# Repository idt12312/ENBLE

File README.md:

# ENBLE

ENBLE is the **EN**vironmental sensor which measures temperature, humidity, and air pressure and sends them over **BLE**.
Because it consumes little current, it can work several years.

Using bridge server and [ThingsBooard](https://thingsboard.io/) which are runnning on Raspberry Pi3, 
you can collect data from some ENBLEs and view measurement data via web browser.

## Contents of this repository

This repository consists of two components.

### 1. Sensor 

[**ENBLE/sensor**](sensor/)

It contains PCB design and firmware for a ENBLE device. 
The details is in README.md.

### 2. Bridge Server

[**ENBLE/bridge_server**](bridge_server/)

It constains a bridge between ENBLE and [**ThingsBooard**](https://thingsboard.io/) as a sample code to utilize ENBLE. 
Bridge server listens BLE advertise packets from ENBLEs and sends data to a ThingsBoard server. 
Using ThingsBoard enables you to collect and visualize measured data.

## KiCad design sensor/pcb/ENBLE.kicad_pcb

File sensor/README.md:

# ENBLE Sensor 

This device measures temperature, humidity and pressure using BME280 and send these measured data over BLE advertising and GATT service.
The data format of BLE advertising and GATT service is described bellow.
Using advertising (not using GATT) to collect measured data enables a device to reduce current consumption.  

## BLE Advertise

| Parameter          | Value                 |
|--------------------|-----------------------|
| Local Name         | "ENBLE"               |
| Advertise Interval | 6000ms                |
| Manufacturer data  | 10 bytes binary data  |

ENBLE has a push button.
If you push the button, advertising interval change into 100ms.
It is useful to find the specified device which you press the button. 

Manufacturer data has DeviceID and measurement results of sensors.  
Data format is as shown below. 

| Position | Contents    | DataType |
|----------|-------------|----------|
| byte 0-1 | DeviceID    | uint16   |
| byte 2-3 | Battery     | uint16   |
| byte 4-5 | Temperature | int16    |
| byte 6-7 | Humidity    | uint16   |
| byte 8-9 | Pressure    | uint16   |

Each data is contained in **little endian 16bit integer**.  
Means of above data are same as ones in bellow characteristics.

## BLE Services

| Name          | Type           | Permissions | UUID                                 | DataType |
|---------------|----------------|-------------|--------------------------------------|----------|
| ENBLE Service | Service        | Read        | bff20001-378e-4955-89d6-25948b941062 |          |
| DeviceID      | Characteristic | Read, Write | bff20011-378e-4955-89d6-25948b941062 | uint16   |
|  Period       | Characteristic | Read, Write | bff20012-378e-4955-89d6-25948b941062 | uint16   |
| Battery       | Characteristic | Read        | bff20021-378e-4955-89d6-25948b941062 | uint16   |
| Temperature   | Characteristic | Read        | bff20022-378e-4955-89d6-25948b941062 | int16    |
| Humidity      | Characteristic | Read        | bff20023-378e-4955-89d6-25948b941062 | uint16   |
| Pressure      | Characteristic | Read        | bff20024-378e-4955-89d6-25948b941062 | uint16   |

### DeviceID
This characteristic indicates a unique number as 16bit unsigned integer. 
The value of this characteristic is stored in nonvolatile memory. 

### Period
This characteristic indicates a sample period of sensors. 
All sensors (battery, temperature, humidity and pressure) sample at the same period. 
This period is 16 bit unsigned integer in seconds. 
The value of this characteristic is stored in nonvolatile memory. 

### Battery
This characteristic indicates battery voltage of the device in mV. 

### Temperature
This characteristic indicates temperature in degC, resolution is 0.01 DegC. 
A negative value is represented in two's complement number. 

### Humidity
This characteristic indicates humidity in %, resolution is 0.1 %.

### Pressure
This characteristic indicates air pressure in Pa, resolution is 10Pa

## Build

### Setup for build
1. Download Nordic SDK ver 12.3.0
2. Place Nordic SDK in firmware/lib  
ex) The structure of directory must be is following.   
    firmware/lib/  
        └──nRF5_SDK_12.3.0_d7731ad/ (this directory name can be anything you like)  
        .       ├──components/  
        .       ├──external/  
        .       ├── ......  

3. Modify NORDIC_SDK_PATH parameter in firmware/Makefile
4. Modify toolchain configuration in 
    * for Linux or OSX user : $(NORDIC_SDK_PATH)/components/toolchain/gcc/Makefile.posix
    * for Windows user : $(NORDIC_SDK_PATH)/components/toolchain/gcc/Makefile.windows

### Build and Flash firmware
This project can be build with GNU MAKE. 
What you need to do for build is executing ```make``` command. 
When you flah a firmware to an ENBLE sensor device, 
connect the device via JLink and execute ```make flash```.

## PCB

I design a PCB with KiCad. 

The following is a simple block diagram.

I designed PCB to fit in the case, [**TAKACHI PS-65 Seriese**](http://www.takachi-el.co.jp/data/pdf/2016-01-065.pdf). 

### Current consumption

| State       | Consumption | Interval   |
|-------------|-------------|------------|
| advertising | 29.4 μC     | 6.0 s      |
| measuring (start)   | 4.14 μC     | 60 s       |
| measuring (end)   | 8.07 μC     | 60 s       |
| sleeping    | 3.80 μA     | constantly |

<table border="0">
    <tr>
        <td></td>
        <td></td>
    </tr>
</table>

From the above, current consumption per one hour is  
3600 / 6 * 29.4μ + 3600 / 60 * (4.14μ + 8.07μ) + 3600 * 3.8μ = 32.1 mC/h.

Because CR2032 battery charge is 810C(225mAh), 
ENBLE can work in
810 / 31.6e-3 = 25233h (**about 3 years**).

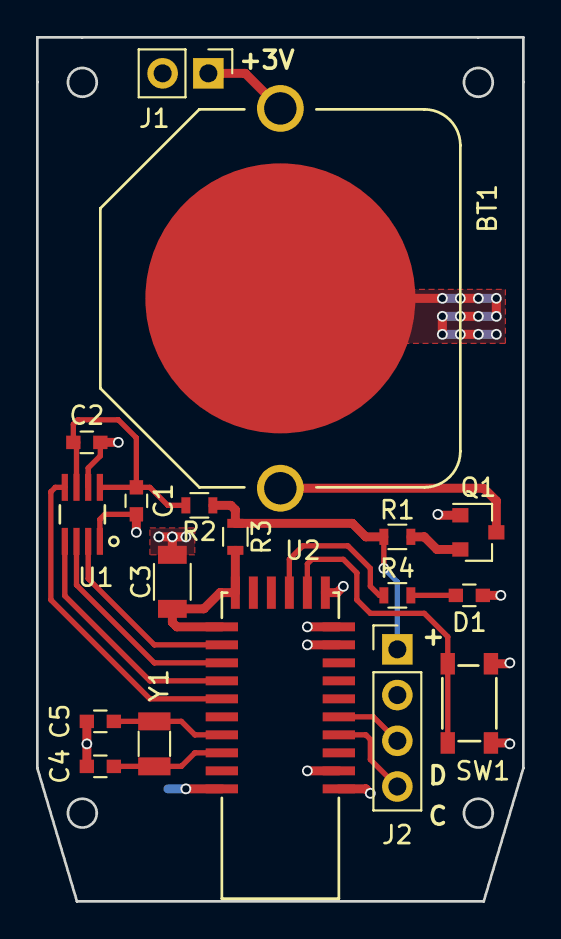
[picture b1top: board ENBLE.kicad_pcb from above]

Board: 2 copper layers, 27.0 x 48.0 mm, 18 parts (0 on the bottom side), 17 nets.

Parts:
BT1: CR2032; BK-888
C1, C2: 0.1u; C_0603
C3: 10u; C_1206
C4, C5: 8p; C_0603
D1: LED; C_0603
J1: Conn_01x02; Pin_Header_Straight_1x02_Pitch2.54mm
J2: Conn_01x04; Pin_Header_Straight_1x04_Pitch2.54mm
Q1: SI2333; SOT-23
R1, R2, R3: 0; R_0603
R4: 2.2k; R_0603
SW1: SW_SPST; SKRPACE010
U1: BME280
U2: BVMCN5103-BK
Y1: 32.768kHz; Crystal_SMD_3215-2pin_3.2x1.5mm

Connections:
/LED: R4.1, U2.13
/SENS_CS: U1.2, U2.18
/SENS_SCK: U1.4, U2.20
/SENS_SDI: U1.3, U2.19
/SENS_SDO: U1.5, U2.21
/SW: SW1.1, U2.12
/SWDCLK: J2.4, U2.4
/SWDIO: J2.3, U2.5
GND: BT1.2, C1.2, C2.2, C3.2, C4.2, C5.2, D1.1, J1.2, J2.2, Q1.1, SW1.2, U1.1, U1.7, U2.1, U2.2, U2.9, U2.10, U2.11, U2.26
unnamed: BT1.1, J1.1, Q1.3
unnamed: C1.1, C2.1, R2.2, U1.6, U1.8
unnamed: C3.1, R3.2, U2.16, U2.17
unnamed: C4.1, U2.24, Y1.1
unnamed: C5.1, U2.23, Y1.2
unnamed: D1.2, R4.2
unnamed: Q1.2, R1.1
VCC: J2.1, R1.2, R2.1, R3.1

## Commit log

2018-12-03 sensor pcb：add pcb data
2018-12-20 sensor firm: copy base from nordic template
2018-12-20 sensor firm: implement BLE service
2018-12-27 sensor firm: implement manipulations for led and button
2018-12-27 sensor firm: implement manipulations for BME280
2018-12-29 sensor firm: implement ENBLE application
    * periodically sensor measurement
    * sending measurement on advertise data
2018-12-29 sensor firm: improve sensor measuring * rename bme280 module * add measuring of battery voltage * add uninit spi and adc after using them to reduce current consumption
2018-12-29 sensor firm: fix sign of temperature
2018-12-29 sensor firm: add user descriptions to charactericsis
2018-12-29 sensor firm: fix not applying wrote data through ENBLE service
    * add properly calling event handler of ENBLE service
    * change how to store sensor measurement
    * add procedure of updating advertising data after new device_id is written
2018-12-29 sensor firm: add restart of advertising after disconnect
2018-12-30 sensor firm: add backup device id and measurement period using FDS
2019-01-04 sensor firm: change an order of data in advertise packets
2019-01-04 sensor firm: update README about advertising
2019-01-07 sensor firm: add frequently advertising when button is pushed
2019-01-07 sensor firm: improve error log
2019-01-07 sensor firm: add clearing nonvolatile data
    If button is pushed in boot sequence, nonvolatile data (measurement period, device id and bonding data) will be cleared.
2019-01-31 sensor firm: optimize current consumption
    * fix compiler option -Og to -O2
    * remove logging via SeggerRTT
    * remove led blinking at the end of sensor measurement
2019-04-01 sensor firm: smooth battery measurement value
    to get smooth one, use the moving average of battery voltage as battery voltage measurement
2019-04-01 sensor firm: fix ignore condition for a button event
2019-04-02 sensor firm: blink led at writing period char or device_id char
2019-04-04 sensor firm: change units of measured value
2019-04-16 sensor firm: change advertising interval
    to reduce current consumption
2019-04-16 sensor pcb: move library files into lib directory
2019-04-17 sensor: add script to calcurate current consumption
2019-04-20 sensor: update README
2019-04-20 server: add bridge server script
2019-04-21 update document
2020-02-02 add pyenv files to .gitignore
